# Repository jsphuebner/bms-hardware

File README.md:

# bms-hardware
Hardware design files for Lithium BMS

# License
Attribution-ShareAlike 4.0 International
https://creativecommons.org/licenses/by-sa/4.0/legalcode

You musn't change the copyright info (J. Huebner/A. Martell and openinverter.org) on the silkscreen in size location or content.

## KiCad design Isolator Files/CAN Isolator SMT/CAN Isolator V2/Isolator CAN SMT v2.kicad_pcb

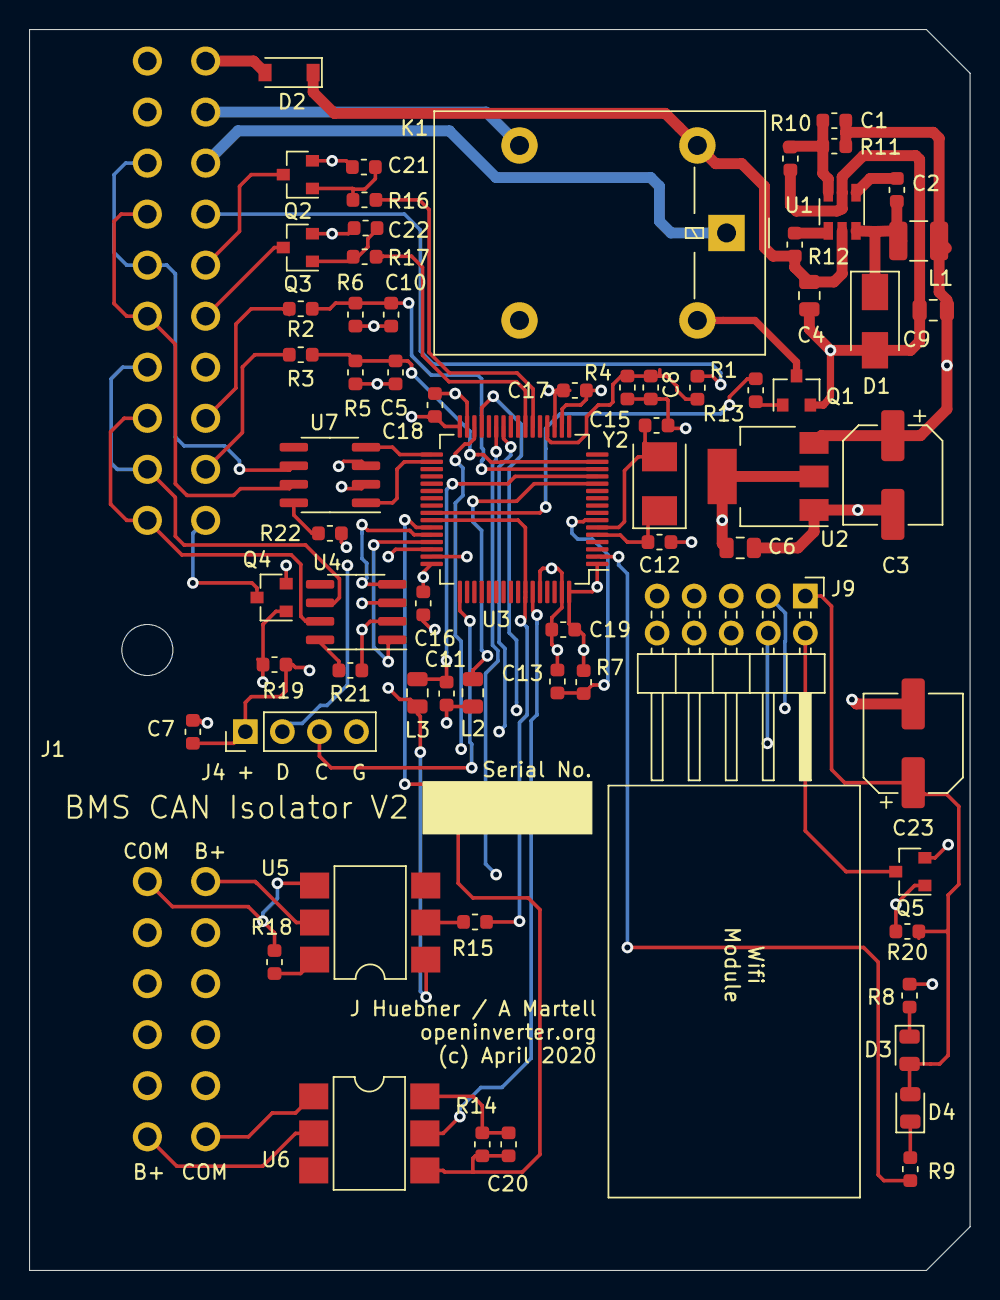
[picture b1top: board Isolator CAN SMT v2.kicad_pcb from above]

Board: 4 copper layers, 64.5 x 85.1 mm, 68 parts (0 on the bottom side), 63 nets.

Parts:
C1: 33pF; C_0603_1608Metric
C2: 22nF; C_0603_1608Metric
C3, C23: 100uF; CP_Elec_6.3x7.7
C4: 4.7uF; C_0805_2012Metric
C5, C10: 1nF; C_0603_1608Metric
C6: 10uF; C_0805_2012Metric
C7, C11, C13, C16, C17, C18, C19: 100nF; C_0603_1608Metric
C8, C21, C22: 1uF; C_0603_1608Metric
C9: 22uF; C_0805_2012Metric
C12, C15, C20: 20pF; C_0603_1608Metric
D1: D_Schottky; D_SMA
D2: 1N4148; D_SOD-123
D3, D4: LED; LED_0805_2012Metric
J1: Cinch_5810132011; Cinch_581_01_32_011
J4: Conn_01x04; PinHeader_1x04_P2.54mm_Vertical
J9: Conn_02x05_Odd_Even; PinHeader_2x05_P2.54mm_Horizontal
K1: G5LE-1; Relay_SPDT_Omron-G5LE-1
L1: 3.3uH; L_1210_3225Metric
L2, L3: 10uH; L_0805_2012Metric
Q1, Q2, Q3: S8050; SOT-23
Q4, Q5: AO3400A; SOT-23
R1, R7, R13, R16, R17, R19, R20, R21, R22: 10KΩ; R_0603_1608Metric
R2, R3, R4: 15KΩ; R_0603_1608Metric
R5, R6: 4.7KΩ; R_0603_1608Metric
R8, R9: 470Ω; R_0603_1608Metric
R10: 9.53KΩ; R_0603_1608Metric
R11: 49.9KΩ; R_0603_1608Metric
R12, R14, R18: 100KΩ; R_0603_1608Metric
R15: 270Ω; R_0603_1608Metric
U1: MP2359; TSOT-23-6
U2: LD1117S33TR_SOT223; SOT-223-3_TabPin2
U3: STM32F105RBTx; LQFP-64_10x10mm_P0.5mm
U4, U7: SN65HVD230; SOIC-8_3.9x4.9mm_P1.27mm
U5, U6: 4N35S; SMDIP-6_W7.62mm
Y2: 8M0; Crystal_SMD_5032-2Pin_5.0x3.2mm

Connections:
12V_In: D2.2, J1.A1
+3V3: C6.1, C7.1, C16.1, C17.1, C18.1, C19.1, C23.1, D3.2, D4.2, J4.1, J9.1, L3.1, R7.1, R19.1, R20.1, U2.2, U3.1, U3.19, U3.32, U3.48, U3.64, U4.3, U5.1, U7.3
+5V: C1.1, C3.1, C9.1, J1.A7, L1.2, R11.1, U2.3
+12V: C4.1, D2.1, K1.2, R12.2, U1.5
A_OUT_1: J1.A5, Q2.3
A_OUT_2: J1.A6, Q3.3
CAN1H: J1.A18, J1.A20, U4.7
CAN1L: J1.A17, J1.A19, U4.6
CAN2H: J1.A14, J1.A16, U7.7
CAN2L: J1.A13, J1.A15, U7.6
Current_1: J1.A8, R2.1
Current_2: J1.A9, R3.1
Current_Sensor_Gnd: J1.A10, Q4.3
Data_In_B+: J1.B12, U6.2
Data_In_Com: J1.B6, U6.1
Data_Out_B+: J1.B1, U5.5
Data_Out_Com: J1.B7, R18.1, U5.4
GND: C3.2, C4.2, C5.2, C6.2, C7.2, C8.2, C9.2, C10.2, C11.2, C12.2, C13.2, C15.2, C16.2, C17.2, C18.2, C19.2, C21.2, C22.2, C23.2, D1.2, J1.A11, J4.4, L2.2, Q1.2, Q2.2, Q3.2, Q5.2, R4.1, R5.1, R6.1, R8.1, R10.2, R21.1, R22.1, U1.2, U2.1, U3.18, U3.31, U3.47, U3.60, U3.63, U4.2, U7.2
Ignition: J1.A4, R1.1
unnamed: C1.2, R10.1, R11.2, U1.3
unnamed: C2.1, D1.1, L1.1, U1.6
unnamed: C2.2, U1.1
unnamed: C11.1, L3.2, U3.13
unnamed: C20.2, R14.1, U6.6
unnamed: C21.1, Q2.1, R16.2
unnamed: C22.1, Q3.1, R17.2
unnamed: D3.1, R8.2
unnamed: D4.1, R9.2
unnamed: J9.2, Q5.3
unnamed: K1.5, Q1.3
unnamed: Q1.1, R13.2
unnamed: R12.1, U1.4
unnamed: R15.1, U5.2
unnamed: R18.2, U5.6
unnamed: R21.2, U4.8
unnamed: R22.2, U7.8
PA0_Cur-: C10.1, R2.2, R6.2, U3.14
PA1_Cur+: C5.1, R3.2, R5.2, U3.15
PA4_Ignition: C8.1, R1.2, R4.2, U3.20
PA6_TIM3_CH1: R16.1, U3.22
PA7_TIM3_CH2: R17.1, U3.23
PA8_OUT_RELAY: R13.1, U3.41
PA9_USART1_TX: R15.2, U3.42, U3.58
PA10_USART1_RX: C20.1, R14.2, U3.43, U6.4
PA11_CAN1_RX: U3.44, U4.4
PA12_CAN1_TX: U3.45, U4.1
PB0_CSENSE_CONTROL: Q4.1, R19.2, U3.26
PB1_WIFI_CONTROL: Q5.1, R20.2, U3.27
PB7_USART1_RX: U3.59, U6.5
PB10_USART3_TX: J9.3, U3.29
PB11_USART3_RX: J9.4, U3.30
PB12_CAN2_RX: U3.33, U7.4
PB13_CAN2_TX: U3.34, U7.1
PC13_LED: R9.1, U3.2
PD0_OSC_IN: C12.1, U3.5, Y2.1
PD1_OSC_OUT: C15.1, U3.6, Y2.2
Relay_Com: J1.A3, K1.1
Relay_NC: J1.A12, K1.4
Relay_NO: J1.A2, K1.3
SWDCLK: J4.3, U3.49
SWDIO: J4.2, U3.46
VSSA: L2.1, Q4.2, U3.12
_RESET: C13.1, R7.2, U3.7

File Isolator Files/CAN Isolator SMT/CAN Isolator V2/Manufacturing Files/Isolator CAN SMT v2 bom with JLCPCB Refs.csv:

Component,Value,References,Footprint,JLPCB Component,JLPCB Extended
1,100nF,C7 C11 C13 C16 C17 C18 C19,C_0603_1608Metric,C14663,
2,100uF,C3 C23,CP_Elec_6.3x7.7,C176675,e
3,10uF,C6,C_0805_2012Metric,C15850,
4,1nF,C5 C10,C_0603_1608Metric,C1588,
5,1uF,C8 C21 C22,C_0603_1608Metric,C15849,
6,20pF,C12 C15 C20,C_0603_1608Metric,C1648,
7,22nF,C2,C_0603_1608Metric,C21122,
8,22uF,C9,C_0805_2012Metric,C59461,
9,33pF,C1,C_0603_1608Metric,C1663,
10,4.7uF,C4,C_0805_2012Metric,C1779,
11,1N4148,D2,D_SOD-123,C81598,
12,D_Schottky,D1,D_SMA,C12889,e
13,LED,D3 D4,LED_0805_2012Metric,C84256,
14,Cinch_5810132011,J1,Cinch_581_01_32_011,,
15,Conn_01x04,J4,PinHeader_1x04_P2.54mm_Vertical,,
16,Conn_02x05_Odd_Even,J9,PinHeader_2x05_P2.54mm_Horizontal,,
17,G5LE-1,K1,Relay_SPDT_Omron-G5LE-1,,
18,10uH,L2 L3,L_0805_2012Metric,C1046,e
19,3.3uH,L1,L_1210_3225Metric,C87560,e
20,AO3400A,Q4 Q5,SOT-23,C20917,
21,S8050,Q1 Q2 Q3,SOT-23,C2146,
22,100KΩ,R12 R14 R18,R_0603_1608Metric,C25803,
23,10KΩ,R1 R7 R13 R16 R17 R19 R20 R21 R22,R_0603_1608Metric,C25804,
24,15KΩ,R2 R3 R4,R_0603_1608Metric,C22809,
25,270Ω,R15,R_0603_1608Metric,C22966,
26,4.7KΩ,R5 R6,R_0603_1608Metric,C23162,
27,470Ω,R8 R9,R_0603_1608Metric,C23179,
28,49.9KΩ,R11,R_0603_1608Metric,C23184,
29,9.53KΩ,R10,R_0603_1608Metric,C23127,e
30,4N35S,U5 U6,SMDIP-6_W7.62mm,C143074,e
31,LD1117S33TR_SOT223,U2,SOT-223-3_TabPin2,C347229,e
32,MP2359,U1,TSOT-23-6,C14259,
33,SN65HVD230,U4 U7,SOIC-8_3.9x4.9mm_P1.27mm,C12084,
34,STM32F105RBTx,U3,LQFP-64_10x10mm_P0.5mm,C8349,e
35,8M0,Y2,Crystal_SMD_5032-2Pin_5.0x3.2mm,C115962,





Component Groups:,35
Component Count:,68
Fitted Components:,68
Number of PCBs:,1
Total components:,68
Schematic Version:,2
Schematic Date:,25 April 2020
PCB Variant:,[u'default']
BoM Date:,03/05/2020 19:10:30
Schematic Source:,C:\Users\andym\OneDrive\10 Documents\01 Projects\01 Electric Car\30 Johannes Huebner\200 BMS\30 CAN Isolator\20 CAN Isolator SMT\10 KiCAD\Isolator CAN SMT STM32F105 2 layer v2\Isolator CAN SMT v2.sch
KiCad Version:,Eeschema (5.1.5)-3

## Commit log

2019-07-11 Changed comments and part numbers
2019-07-11 Fixed dangling pin of R6
2019-07-11 Update BatMeas5.1.csv
    Updated IC3 to AP2139AK-3.0TRG1 as ground current is less. Feels more important than a few pennys on cost
2019-07-17 Created version 5.2 with dual connector population
2019-07-18 Enlarged board to space new connectors
    Enlarged board, now 35x70mm. Moved bottom tracks other than ground plane to top side. Holes spaced 2.5mm in from edge of PCB (was 2.54mm)
2019-07-21 Minor updates and added maunfacturing files
2019-07-21 Added zip version of man files
2019-07-22 Updated Isolator board and added manufacturing files
2019-08-16 Added Isolator2.0 BOM
    Added Isolator BOM
2019-08-26 Update BatMeas5.2 Manufacturing BOM.csv
    Changed bleed resistors to 27R, specified voltage divider resistors as 1% tolerance
2019-10-29 Isolator BOM Update
    Added manufacturer details. Updated crystal to 11.0592MHz and changed microcontroller to Atmega88P
2019-12-12 Removed Zener
2020-01-02 Updated slave board: - Populate SMT programming header (also used for calibration) - select 1st board via jumper on programming header - B+ exports 3V3 instead of pack voltage -> no Zener needed. Res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
2020-01-02 Added CAN isolator schematic and layout
2020-01-05 Minor CAN isolator PCB mods to improve track clearance. Added manufacturing data
2020-02-05 Changed C5 to 10n
2020-02-24 Replaced JST comms connector by AVX or 4mm IDC wire to board connector Removed all THT options Removed holes below cell JST connector, made pads longer
2020-02-24 Updated BOM
2020-03-01 Add BOM for Blue Pill CAN Isolator
    Create and add BOM for Blue Pill version of CAN Isolator
2020-03-01 Tidy up file structure
2020-03-01 Added SMT version of CAN isolator
2020-03-02 Added manufacturing files
2020-03-02 Changed value of C6 to 1u
2020-03-02 Added JLCPCB placement and BOM files
2020-05-02 Use Attiny44
2020-05-02 Use 3V3 reg with enable pin
2020-05-02 Move vias further away from opposite pin
2020-05-03 Add CAN Isolator V2 files
    CAN Isolator V2 created. Uses Cinch enclosure.
2020-08-06 Replaced 4M12/1M divider by 3M9/953k divider to stay in JLCPCBs part lib
2020-08-06 Update BOM and placement file after ordering
2020-10-31 Changed R6 from 1k to 4k7, C5 from 10n to 1n, R14 from 100k to 47k
2021-05-05 BOM update
